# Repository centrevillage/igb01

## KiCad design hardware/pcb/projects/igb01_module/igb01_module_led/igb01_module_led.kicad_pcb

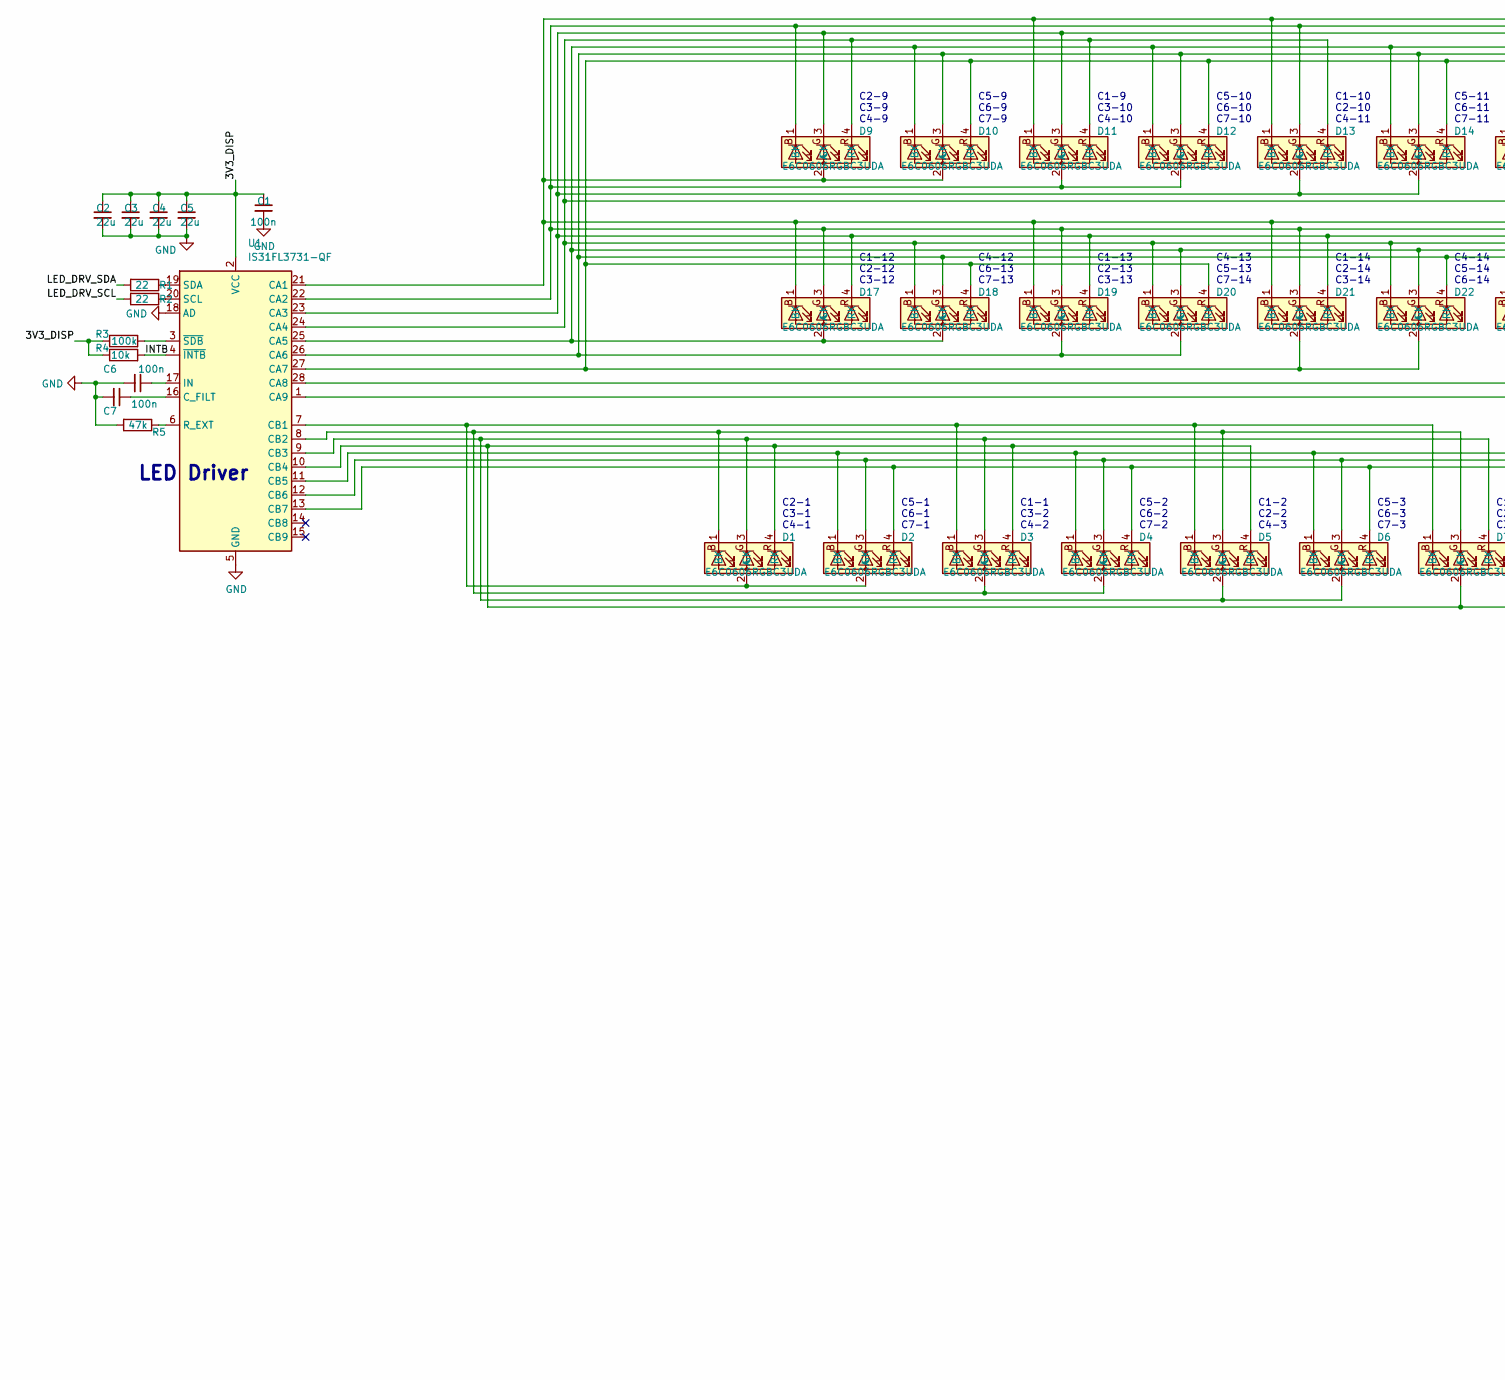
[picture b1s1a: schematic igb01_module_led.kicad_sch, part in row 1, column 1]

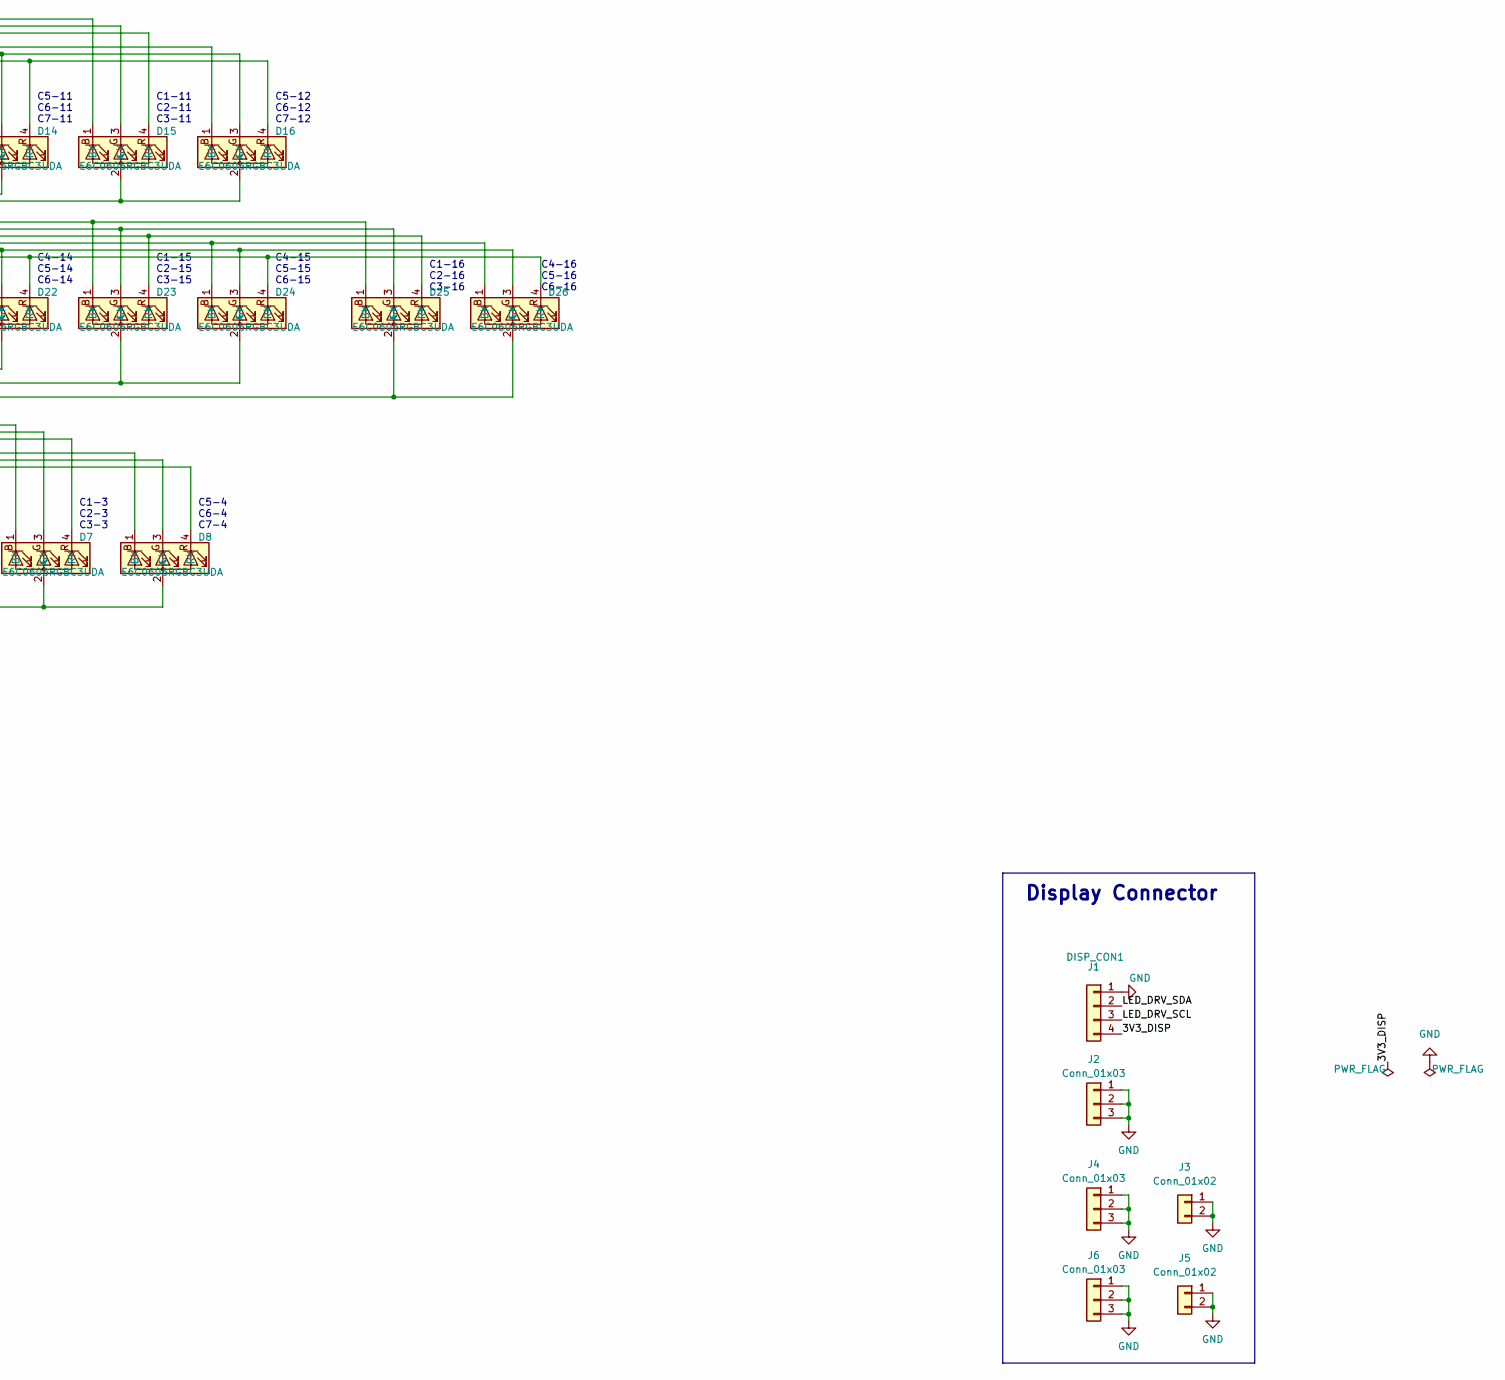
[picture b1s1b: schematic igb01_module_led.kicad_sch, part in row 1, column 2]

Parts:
C1, C6, C7: 100n; C_0402_1005Metric
C2, C3, C4, C5: 22u; C_0805_2012Metric
D1, D2, D3, D4, D5, D6, D7, D8, D9, D10, D11, D12, D13, D14, D15, D16, D17, D18, D19, D20, D21, D22, D23, D24, D25, D26: E6C0606RGBC3UDA; led_rgb
J1: DISP_CON1; PinSocket_1x04_P2.00mm_Vertical
J2, J4, J6: Conn_01x03; PinSocket_1x03_P2.00mm_Vertical
J3, J5: Conn_01x02; PinSocket_1x02_P2.00mm_Vertical
R1, R2: 22; R_0402_1005Metric
R3: 100k; R_0402_1005Metric
R4: 10k; R_0402_1005Metric
R5: 47k; R_0603_1608Metric
U1: IS31FL3731-QF; QFN-28-1EP_4x4mm_P0.4mm_EP2.3x2.3mm

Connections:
/3V3_DISP: C1.1, C2.1, C3.1, C4.1, C5.1, J1.4, R3.1, R4.1, U1.2 (VCC)
/INTB: R4.2, U1.4 (~INTB)
/LED_DRV_SCL: J1.3, R2.2
/LED_DRV_SDA: J1.2, R1.2
GND: C1.2, C2.2, C3.2, C4.2, C5.2, C6.2, C7.2, J1.1, J2.1, J2.2, J2.3, J3.1, J3.2, J4.1, J4.2, J4.3, J5.1, J5.2, J6.1, J6.2, J6.3, R5.2, U1.5 (GND), U1.18 (AD), U1.29 (GND)
unnamed: D1.2 (A), D2.2 (A), D3.1 (BK), D5.1 (BK), D7.1 (BK), U1.7 (CB1)
unnamed: D1.1 (BK), D3.2 (A), D4.2 (A), D5.3 (GK), D7.3 (GK), U1.8 (CB2)
unnamed: D1.3 (GK), D3.3 (GK), D5.2 (A), D6.2 (A), D7.4 (RK), U1.9 (CB3)
unnamed: D1.4 (RK), D3.4 (RK), D5.4 (RK), D7.2 (A), D8.2 (A), U1.10 (CB4)
unnamed: D2.1 (BK), D4.1 (BK), D6.1 (BK), D8.1 (BK), U1.11 (CB5)
unnamed: D2.3 (GK), D4.3 (GK), D6.3 (GK), D8.3 (GK), U1.12 (CB6)
unnamed: D2.4 (RK), D4.4 (RK), D6.4 (RK), D8.4 (RK), U1.13 (CB7)
unnamed: D9.2 (A), D10.2 (A), D11.1 (BK), D13.1 (BK), D15.1 (BK), D17.1 (BK), D19.1 (BK), D21.1 (BK), D23.1 (BK), D25.1 (BK), U1.21 (CA1)
unnamed: D10.1 (BK), D12.1 (BK), D14.1 (BK), D16.1 (BK), D17.2 (A), D18.2 (A), D20.3 (GK), D22.3 (GK), D24.3 (GK), D26.3 (GK), U1.25 (CA5)
unnamed: D10.3 (GK), D12.3 (GK), D14.3 (GK), D16.3 (GK), D18.3 (GK), D19.2 (A), D20.2 (A), D22.4 (RK), D24.4 (RK), D26.4 (RK), U1.26 (CA6)
unnamed: D10.4 (RK), D12.4 (RK), D14.4 (RK), D16.4 (RK), D18.4 (RK), D20.4 (RK), D21.2 (A), D22.2 (A), U1.27 (CA7)
unnamed: D9.1 (BK), D11.2 (A), D12.2 (A), D13.3 (GK), D15.3 (GK), D17.3 (GK), D19.3 (GK), D21.3 (GK), D23.3 (GK), D25.3 (GK), U1.22 (CA2)
unnamed: D9.3 (GK), D11.3 (GK), D13.2 (A), D14.2 (A), D15.4 (RK), D17.4 (RK), D19.4 (RK), D21.4 (RK), D23.4 (RK), D25.4 (RK), U1.23 (CA3)
unnamed: D9.4 (RK), D11.4 (RK), D13.4 (RK), D15.2 (A), D16.2 (A), D18.1 (BK), D20.1 (BK), D22.1 (BK), D24.1 (BK), D26.1 (BK), U1.24 (CA4)
unnamed: D23.2 (A), D24.2 (A), U1.28 (CA8)
unnamed: D25.2 (A), D26.2 (A), U1.1 (CA9)
unnamed: C7.1, U1.16 (C_FILT)
unnamed: C6.1, U1.17 (IN)
unnamed: R5.1, U1.6 (R_EXT)
unnamed: R2.1, U1.20 (SCL)
unnamed: R1.1, U1.19 (SDA)
unnamed: R3.2, U1.3 (~SDB)

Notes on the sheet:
C5-1 C6-1 C7-1
C2-1 C3-1 C4-1
C1-12 C2-12 C3-12
C1-15 C2-15 C3-15
C2-9 C3-9 C4-9
C1-13 C2-13 C3-13
C1-3 C2-3 C3-3
C1-14 C2-14 C3-14
C4-13 C5-13 C7-14
LED Driver
Display Connector
C1-11 C2-11 C3-11
C4-12 C6-13 C7-13
C1-10 C2-10 C4-11
C5-9 C6-9 C7-9
C4-15 C5-15 C6-15
C5-12 C6-12 C7-12
C5-10 C6-10 C7-10
C5-4 C6-4 C7-4
C4-16 C5-16 C6-16
C1-2 C2-2 C4-3
C1-9 C3-10 C4-10
C4-14 C5-14 C6-14
C5-11 C6-11 C7-11
C1-16 C2-16 C3-16
C5-2 C6-2 C7-2
C5-3 C6-3 C7-3
C1-1 C3-2 C4-2

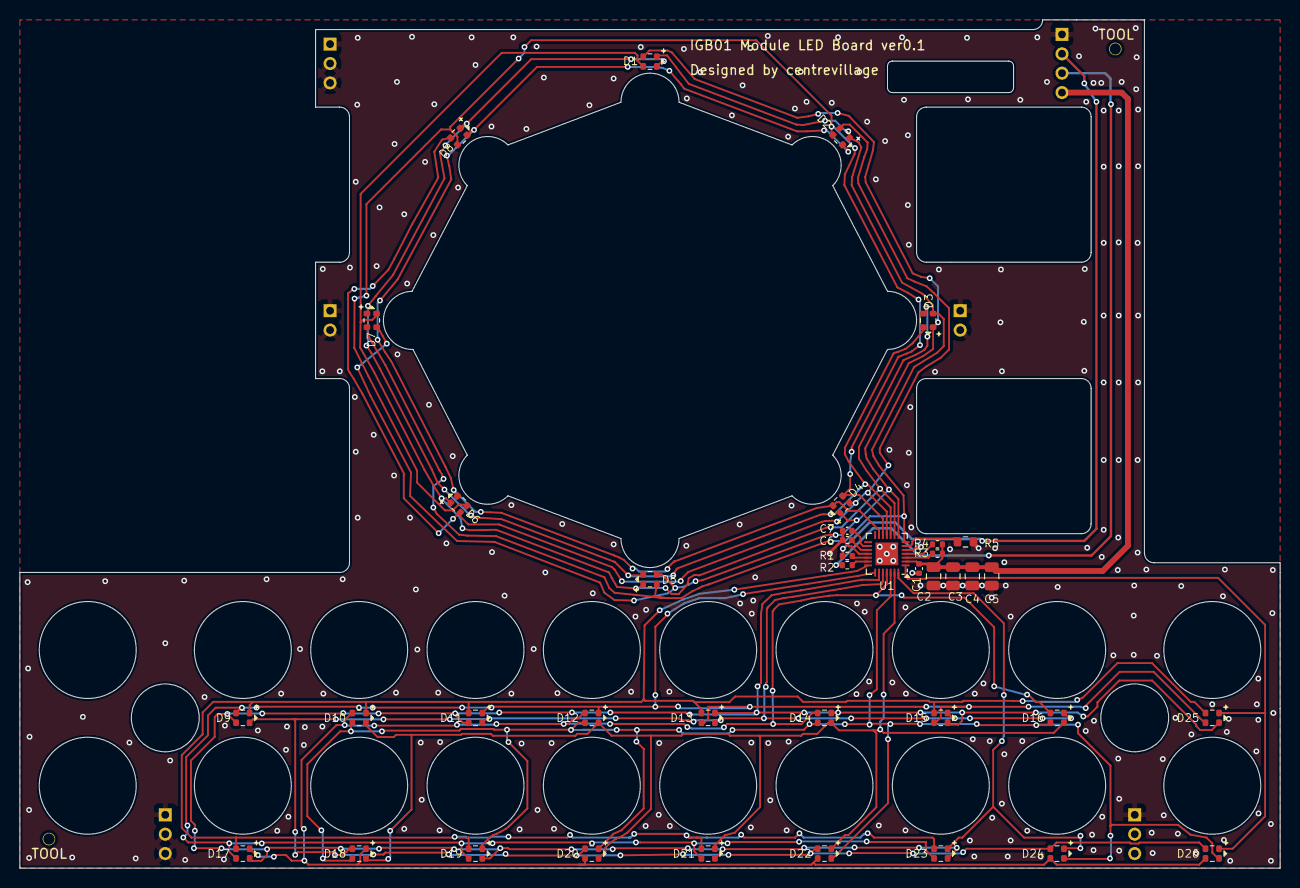
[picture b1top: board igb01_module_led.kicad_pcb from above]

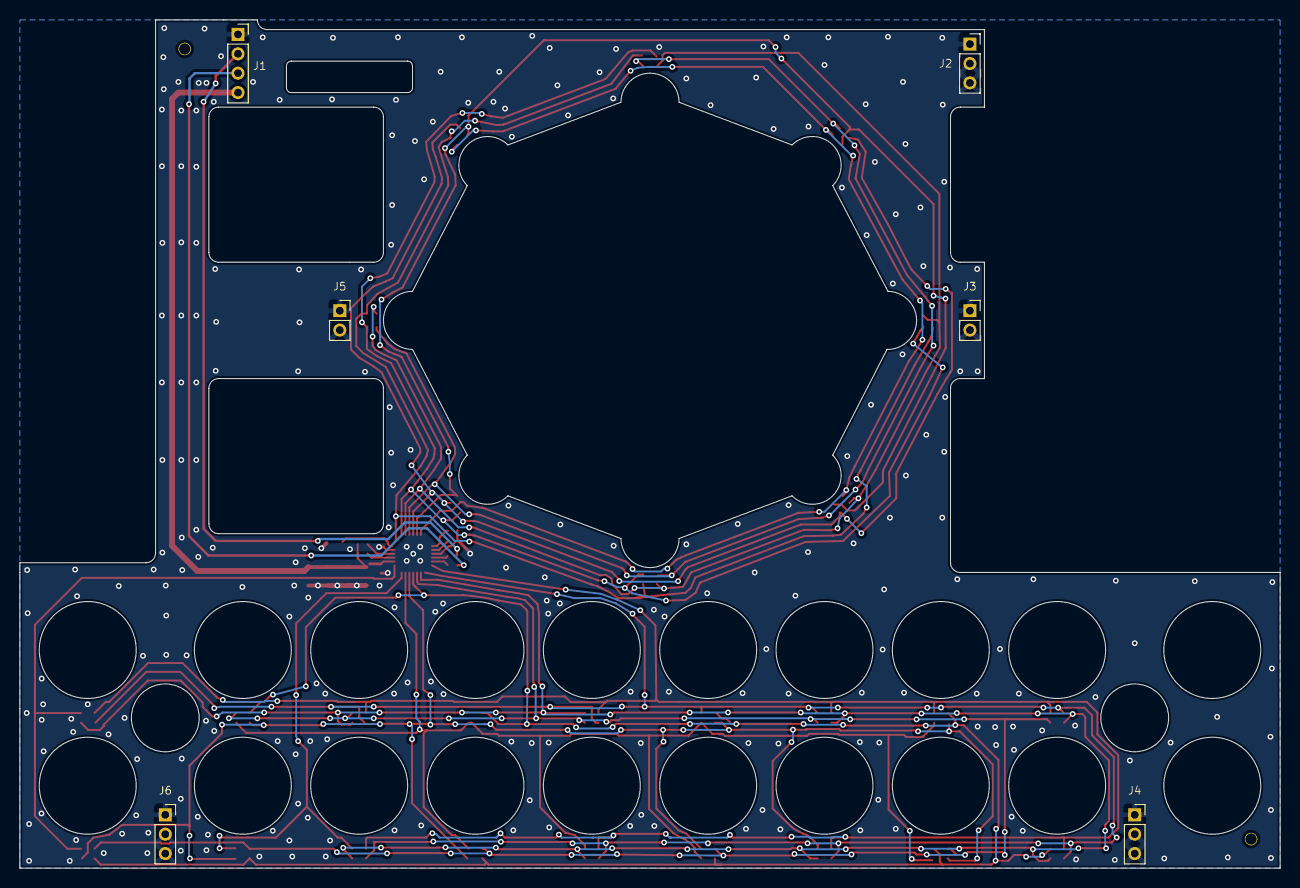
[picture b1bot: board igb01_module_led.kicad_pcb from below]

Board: 2 copper layers, 130.0 x 87.5 mm, 45 parts (6 on the bottom side), 27 nets.

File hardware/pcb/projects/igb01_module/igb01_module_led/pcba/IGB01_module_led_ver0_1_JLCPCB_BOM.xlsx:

Comment | Designator | Footprint | LCSC Part #（optional）
22uF,0805 | C5,C3,C4,C2 | C0805 | C45783
100nF,0402 | C7,C1,C6 | C0402 | C1525
E6C0606RGBC3UDA | D13,D22,D4,D21,D23,D20,D24,D16,D25,D26,D19,D9,D15,D3,D17,D10,D12,D8,D18,D6,D11,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 |  | C375569
22Ω,0402 | R1,R2 | R0402 | C25092
100kΩ,0402 | R3 | R0402 | C25741
10kΩ,0402 | R4 | R0402 | C25744
47kΩ,0603 | R5 | R0603 | C25819
IS31FL3731-QF | U1 | QFN-28 | C191206

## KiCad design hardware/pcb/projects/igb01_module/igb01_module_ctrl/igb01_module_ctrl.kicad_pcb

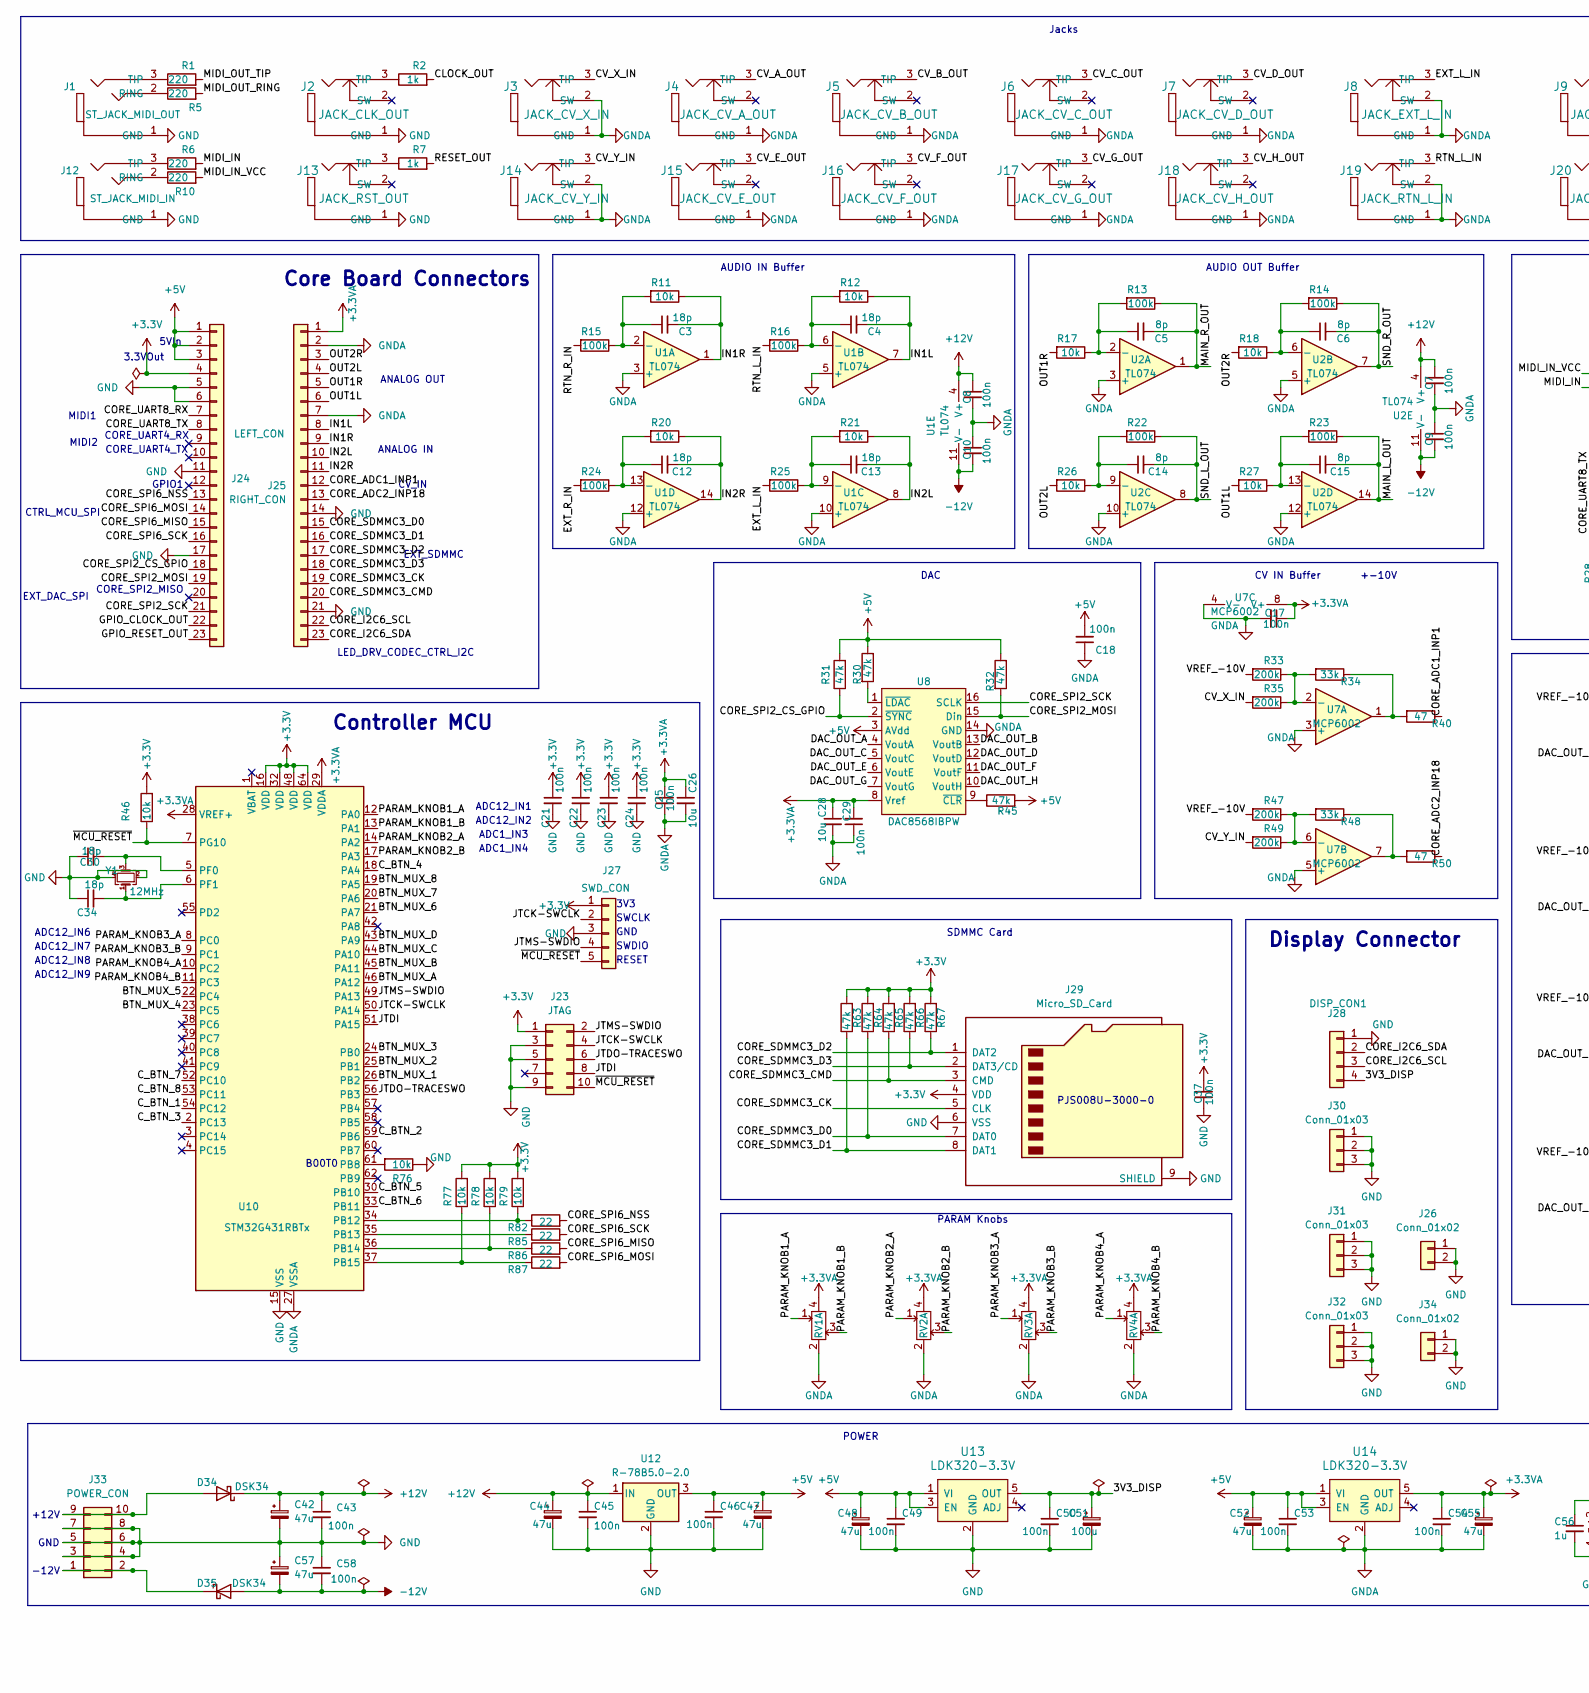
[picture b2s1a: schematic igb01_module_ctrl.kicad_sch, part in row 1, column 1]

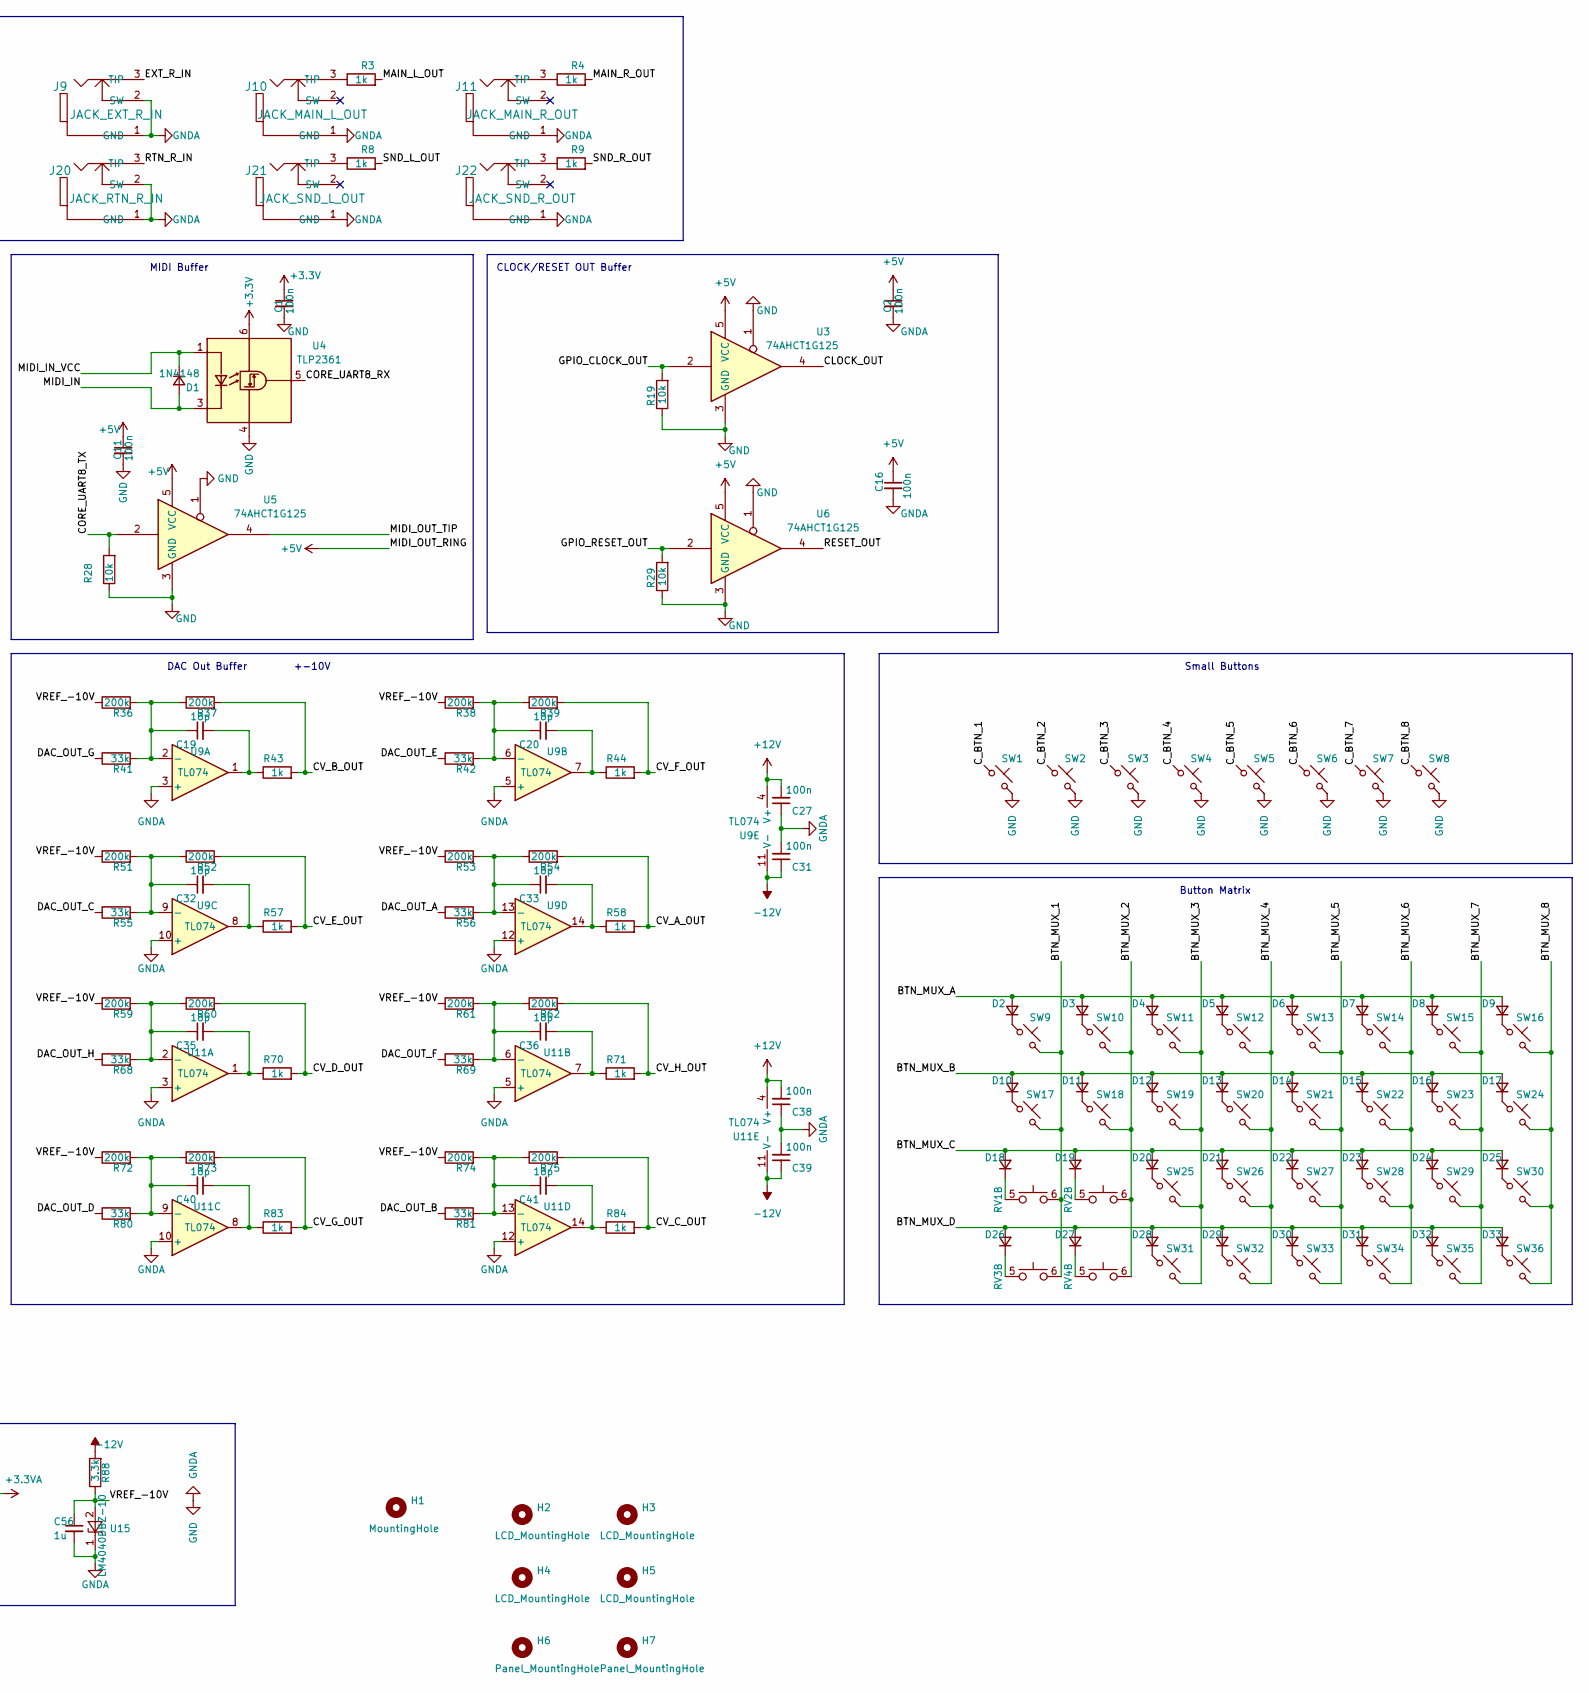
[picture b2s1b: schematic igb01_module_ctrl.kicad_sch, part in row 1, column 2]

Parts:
C1, C2, C7, C8, C9, C10, C11, C16, C17, C18, C21, C22, C23, C24, C25, C27, C29, C31, C37, C38, C39, C43, C45, C46, C49, C50, C53, C54, C58: 100n; C_0603_1608Metric
C3, C4, C12, C13, C19, C20, C30, C32, C33, C34, C35, C36, C40, C41: 18p; C_0603_1608Metric
C5, C6, C14, C15: 8p; C_0603_1608Metric
C26, C28: 10u; C_0805_2012Metric
C42, C44, C47, C48, C52, C55, C57: 47u; C_Elec_5x5.8
C51: 100u; C_Elec_5x5.8
C56: 1u; C_0805_2012Metric
D1: 1N4148; SOD-123
D2, D3, D4, D5, D6, D7, D8, D9, D10, D11, D12, D13, D14, D15, D16, D17, D18, D19, D20, D21, D22, D23, D24, D25, D26, D27, D28, D29, D30, D31, D32, D33: 1N4148; D_SOD-523
D34, D35: DSK34; SOD-123
H1: MountingHole; MountingHole_3.2mm_M3_mod
H2, H3, H4, H5: LCD_MountingHole; MountingHole_2.2mm_M2_mod
H6, H7: Panel_MountingHole; MountingHole_3.2mm_M3_mod
J1: ST_JACK_MIDI_OUT; THONKICONN_center_smleg
J2: JACK_CLK_OUT; THONKICONN_center_smleg
J3: JACK_CV_X_IN; THONKICONN_center_smleg
J4: JACK_CV_A_OUT; THONKICONN_center_smleg
J5: JACK_CV_B_OUT; THONKICONN_center_smleg
J6: JACK_CV_C_OUT; THONKICONN_center_smleg
J7: JACK_CV_D_OUT; THONKICONN_center_smleg
J8: JACK_EXT_L_IN; THONKICONN_center_smleg
J9: JACK_EXT_R_IN; THONKICONN_center_smleg
J10: JACK_MAIN_L_OUT; THONKICONN_center_smleg
J11: JACK_MAIN_R_OUT; THONKICONN_center_smleg
J12: ST_JACK_MIDI_IN; THONKICONN_center_smleg
J13: JACK_RST_OUT; THONKICONN_center_smleg
J14: JACK_CV_Y_IN; THONKICONN_center_smleg
J15: JACK_CV_E_OUT; THONKICONN_center_smleg
J16: JACK_CV_F_OUT; THONKICONN_center_smleg
J17: JACK_CV_G_OUT; THONKICONN_center_smleg
J18: JACK_CV_H_OUT; THONKICONN_center_smleg
J19: JACK_RTN_L_IN; THONKICONN_center_smleg
J20: JACK_RTN_R_IN; THONKICONN_center_smleg
J21: JACK_SND_L_OUT; THONKICONN_center_smleg
J22: JACK_SND_R_OUT; THONKICONN_center_smleg
J23: JTAG; PinHeader_2x05_P1.27mm_Vertical
J24: LEFT_CON; PinSocket_1x23_P2.54mm_Vertical
J25: RIGHT_CON; PinSocket_1x23_P2.54mm_Vertical
J26, J34: Conn_01x02; PinHeader_1x02_P2.00mm_Vertical
J27: SWD_CON; PinSocket_1x05_P2.54mm_Vertical
J28: DISP_CON1; PinHeader_1x04_P2.00mm_Vertical
J29: Micro_SD_Card; MICRO_SD_VERTICAL
J30, J31, J32: Conn_01x03; PinHeader_1x03_P2.00mm_Vertical
J33: POWER_CON; PinHeader_2x05_P2.54mm_Vertical
R1, R5, R6, R10: 220; R_1206_3216Metric
R2, R3, R4, R7, R8, R9, R43, R44, R57, R58, R70, R71, R83, R84: 1k; R_0805_2012Metric
R11, R12, R17, R18, R19, R20, R21, R26, R27, R28, R29, R46, R76, R77, R78, R79: 10k; R_0603_1608Metric
R13, R14, R15, R16, R22, R23, R24, R25: 100k; R_0603_1608Metric
R30, R31, R32, R45, R63, R64, R65, R66, R67: 47k; R_0603_1608Metric
R33, R35, R36, R37, R38, R39, R47, R49, R51, R52, R53, R54, R59, R60, R61, R62, R72, R73, R74, R75: 200k; R_0603_1608Metric
R34, R41, R42, R48, R55, R56, R68, R69, R80, R81: 33k; R_0603_1608Metric
R40, R50: 47; R_0603_1608Metric
R82, R85, R86, R87: 22; R_0603_1608Metric
R88: 3.3k; R_0603_1608Metric
RV1, RV2, RV3, RV4: RV142FPF-40B1
SW1, SW2, SW3, SW4, SW5, SW6, SW7, SW8: SW_Push_45deg; SW_PUSH_6mm_h13mm_mod
SW9, SW10, SW11, SW12, SW13, SW14, SW15, SW16, SW17, SW18, SW19, SW20, SW21, SW22, SW23, SW24, SW25, SW26, SW27, SW28, SW29, SW30, SW31, SW32, SW33, SW34, SW35, SW36: SW_Push_45deg; CandK_Comp_Button
U1, U2, U9, U11: TL074; TSSOP-14_4.4x5mm_P0.65mm
U3, U5, U6: 74AHCT1G125; SOT-23-5
U4: TLP2361; SO-5-6_4.55x3.7mm_P1.27mm
U7: MCP6002; SOIC-8_3.9x4.9mm_P1.27mm
U8: DAC8568IBPW; TSSOP-16_4.4x5mm_P0.65mm
U10: STM32G431RBTx; LQFP-64_10x10mm_P0.5mm
U12: R-78B5.0-2.0; Converter_DCDC_RECOM_R-78B-2.0_THT
U13, U14: LDK320-3.3V; SOT-23-5
U15: LM4040DBZ-10; SOT-23
Y1: 12MHz; Crystal_SMD_2520-4Pin_2.5x2.0mm

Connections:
+3.3V: C1.1, C21.1, C22.1, C23.1, C24.1, C37.1, J23.1, J24.4, J27.1, J29.4 (VDD), R46.2, R63.2, R64.2, R65.2, R66.2, R67.2, R77.2, R78.2, R79.2, U4.6 (VDD), U10.16 (VDD), U10.32 (VDD), U10.48 (VDD), U10.64 (VDD)
+3.3VA: C17.1, C25.1, C26.1, C28.1, C29.2, C54.1, C55.1, J25.1, RV1.4, RV2.4, RV3.4, RV4.4, U7.8 (V+), U8.8 (Vref), U10.28 (VREF+), U10.29 (VDDA), U14.5 (OUT)
+5V: C2.1, C11.1, C16.1, C18.2, C46.1, C47.1, C48.1, C49.1, C52.1, C53.1, J24.1, J24.2, J24.3, R5.2, R30.1, R31.2, R32.1, R45.2, U3.5 (VCC), U5.5 (VCC), U6.5 (VCC), U8.3 (AVdd), U12.3 (OUT), U13.1 (VI), U13.3 (EN), U14.1 (VI), U14.3 (EN)
+12V: C7.1, C8.1, C27.2, C38.2, C42.1, C43.1, C44.1, C45.1, D34.1 (K), U1.4 (V+), U2.4 (V+), U9.4 (V+), U11.4 (V+), U12.1 (IN)
-12V: C9.2, C10.2, C31.1, C39.1, C57.2, C58.2, D35.2 (A), R88.2, U1.11 (V-), U2.11 (V-), U9.11 (V-), U11.11 (V-)
/3V3_DISP: C50.1, C51.1, J28.4, U13.5 (OUT)
/BTN_MUX_1: RV1.6, RV3.6, SW9.2, SW17.2, U10.26 (PB2)
/BTN_MUX_2: RV2.6, RV4.6, SW10.2, SW18.2, U10.25 (PB1)
/BTN_MUX_3: SW11.2, SW19.2, SW25.2, SW31.2, U10.24 (PB0)
/BTN_MUX_4: SW12.2, SW20.2, SW26.2, SW32.2, U10.23 (PC5)
/BTN_MUX_5: SW13.2, SW21.2, SW27.2, SW33.2, U10.22 (PC4)
/BTN_MUX_6: SW14.2, SW22.2, SW28.2, SW34.2, U10.21 (PA7)
/BTN_MUX_7: SW15.2, SW23.2, SW29.2, SW35.2, U10.20 (PA6)
/BTN_MUX_8: SW16.2, SW24.2, SW30.2, SW36.2, U10.19 (PA5)
/BTN_MUX_A: D2.2 (A), D3.2 (A), D4.2 (A), D5.2 (A), D6.2 (A), D7.2 (A), D8.2 (A), D9.2 (A), U10.46 (PA12)
/BTN_MUX_B: D10.2 (A), D11.2 (A), D12.2 (A), D13.2 (A), D14.2 (A), D15.2 (A), D16.2 (A), D17.2 (A), U10.45 (PA11)
/BTN_MUX_C: D18.2 (A), D19.2 (A), D20.2 (A), D21.2 (A), D22.2 (A), D23.2 (A), D24.2 (A), D25.2 (A), U10.44 (PA10)
/BTN_MUX_D: D26.2 (A), D27.2 (A), D28.2 (A), D29.2 (A), D30.2 (A), D31.2 (A), D32.2 (A), D33.2 (A), U10.43 (PA9)
/CLOCK_OUT: R2.2, U3.4
/CORE_ADC1_INP1: J25.12, R40.1
/CORE_ADC2_INP18: J25.13, R50.1
/CORE_I2C6_SCL: J25.22, J28.3
/CORE_I2C6_SDA: J25.23, J28.2
/CORE_SDMMC3_CK: J25.19, J29.5 (CLK)
/CORE_SDMMC3_CMD: J25.20, J29.3 (CMD), R65.1
/CORE_SDMMC3_D0: J25.15, J29.7 (DAT0), R64.1
/CORE_SDMMC3_D1: J25.16, J29.8 (DAT1), R63.1
/CORE_SDMMC3_D2: J25.17, J29.1 (DAT2), R67.1
/CORE_SDMMC3_D3: J25.18, J29.2 (DAT3/CD), R66.1
/CORE_SPI2_CS_GPIO: J24.18, R31.1, U8.2 (~SYNC)
/CORE_SPI2_MOSI: J24.19, R32.2, U8.15 (Din)
/CORE_SPI2_SCK: J24.21, U8.16 (SCLK)
/CORE_SPI6_MISO: J24.15, R86.2
/CORE_SPI6_MOSI: J24.14, R87.2
/CORE_SPI6_NSS: J24.13, R82.2
/CORE_SPI6_SCK: J24.16, R85.2
/CORE_UART8_RX: J24.7, U4.5 (VO)
/CORE_UART8_TX: J24.8, R28.2, U5.2
/CV_A_OUT: J4.3 (TIP), R54.2, R58.2
/CV_B_OUT: J5.3 (TIP), R37.2, R43.2
/CV_C_OUT: J6.3 (TIP), R75.2, R84.2
/CV_D_OUT: J7.3 (TIP), R60.2, R70.2
/CV_E_OUT: J15.3 (TIP), R52.2, R57.2
/CV_F_OUT: J16.3 (TIP), R39.2, R44.2
/CV_G_OUT: J17.3 (TIP), R73.2, R83.2
/CV_H_OUT: J18.3 (TIP), R62.2, R71.2
/CV_X_IN: J3.3 (TIP), R35.2
/CV_Y_IN: J14.3 (TIP), R49.2
/C_BTN_1: SW1.1, U10.54 (PC12)
/C_BTN_2: SW2.1, U10.59 (PB6)
/C_BTN_3: SW3.1, U10.2 (PC13)
/C_BTN_4: SW4.1, U10.18 (PA4)
/C_BTN_5: SW5.1, U10.30 (PB10)
/C_BTN_6: SW6.1, U10.33 (PB11)
/C_BTN_7: SW7.1, U10.52 (PC10)
/C_BTN_8: SW8.1, U10.53 (PC11)
/DAC_OUT_A: R56.1, U8.4 (VoutA)
/DAC_OUT_B: R81.1, U8.13 (VoutB)
/DAC_OUT_C: R55.1, U8.5 (VoutC)
/DAC_OUT_D: R80.1, U8.12 (VoutD)
/DAC_OUT_E: R42.1, U8.6 (VoutE)
/DAC_OUT_F: R69.1, U8.11 (VoutF)
/DAC_OUT_G: R41.1, U8.7 (VoutG)
/DAC_OUT_H: R68.1, U8.10 (VoutH)
/EXT_L_IN: J8.3 (TIP), R25.2
/EXT_R_IN: J9.3 (TIP), R24.2
/GPIO_CLOCK_OUT: J24.22, R19.2, U3.2
/GPIO_RESET_OUT: J24.23, R29.2, U6.2
/IN1L: C4.2, J25.8, R12.1, U1.7
/IN1R: C3.2, J25.9, R11.1, U1.1
/IN2L: C13.2, J25.10, R21.1, U1.8
/IN2R: C12.2, J25.11, R20.1, U1.14
/JTCK-SWCLK: J23.4, J27.2, U10.50 (PA14)
/JTDI: J23.8, U10.51 (PA15)
/JTDO-TRACESWO: J23.6, U10.56 (PB3)
/JTMS-SWDIO: J23.2, J27.4, U10.49 (PA13)
/MAIN_L_OUT: C15.2, R3.2, R23.1, U2.14
/MAIN_R_OUT: C5.2, R4.2, R13.1, U2.1
/MIDI_IN: D1.2 (A), R6.2, U4.3 (K)
/MIDI_IN_VCC: D1.1 (K), R10.2, U4.1 (A)
/MIDI_OUT_TIP: R1.2, U5.4
/OUT1L: J25.6, R27.2
/OUT1R: J25.5, R17.2
/OUT2L: J25.4, R26.2
/OUT2R: J25.3, R18.2
/PARAM_KNOB1_A: RV1.1, U10.12 (PA0)
/PARAM_KNOB1_B: RV1.3, U10.13 (PA1)
/PARAM_KNOB2_A: RV2.1, U10.14 (PA2)
/PARAM_KNOB2_B: RV2.3, U10.17 (PA3)
/PARAM_KNOB3_A: RV3.1, U10.8 (PC0)
/PARAM_KNOB3_B: RV3.3, U10.9 (PC1)
/PARAM_KNOB4_A: RV4.1, U10.10 (PC2)
/PARAM_KNOB4_B: RV4.3, U10.11 (PC3)
/RESET_OUT: R7.2, U6.4
/RTN_L_IN: J19.3 (TIP), R16.2
/RTN_R_IN: J20.3 (TIP), R15.2
/SND_L_OUT: C14.2, R8.2, R22.1, U2.8
/SND_R_OUT: C6.2, R9.2, R14.1, U2.7
/VREF_-10V: C56.1, R33.2, R36.1, R38.1, R47.2, R51.1, R53.1, R59.1, R61.1, R72.1, R74.1, R88.1, U15.2 (A)
/~MCU_RESET: J23.10, J27.5, R46.1, U10.7 (PG10)
GND: C1.2, C2.2, C7.2, C8.2, C9.1, C10.1, C11.2, C16.2, C17.2, C18.1, C21.2, C22.2, C23.2, C24.2, C25.2, C26.2, C27.1, C28.2, C29.1, C30.1, C31.2, C34.1, C37.2, C38.1, C39.2, C42.2, C43.2, C44.2, C45.2, C46.2, C47.2, C48.2, C49.2, C50.2, C51.2, C52.2, C53.2, C54.2, C55.2, C56.2, C57.1, C58.1, J1.1 (GND), J2.1 (GND), J3.1 (GND), J3.2 (SW), J4.1 (GND), J5.1 (GND), J6.1 (GND), J7.1 (GND), J8.1 (GND), J8.2 (SW), J9.1 (GND), J9.2 (SW), J10.1 (GND), J11.1 (GND), J12.1 (GND), J13.1 (GND), J14.1 (GND), J14.2 (SW), J15.1 (GND), J16.1 (GND), J17.1 (GND), J18.1 (GND), J19.1 (GND), J19.2 (SW), J20.1 (GND), J20.2 (SW), J21.1 (GND), J22.1 (GND), J23.3, J23.5, J23.9, J24.5, J24.6, J24.11, J24.17, J25.2, J25.7, J25.14, J25.21, J26.1, J26.2, J27.3, J28.1, J29.6 (VSS), J29.9 (SHIELD), J30.1, J30.2, J30.3, J31.1, J31.2, J31.3, J32.1, J32.2, J32.3, J33.3, J33.4, J33.5, J33.6, J33.7, J33.8, J34.1, J34.2, R19.1, R28.1, R29.1, R76.1, RV1.2, RV2.2, RV3.2, RV4.2, SW1.2, SW2.2, SW3.2, SW4.2, SW5.2, SW6.2, SW7.2, SW8.2, U1.3 (+), U1.5 (+), U1.10 (+), U1.12 (+), U2.3 (+), U2.5 (+), U2.10 (+), U2.12 (+), U3.1, U3.3 (GND), U4.4 (GND), U5.1, U5.3 (GND), U6.1, U6.3 (GND), U7.3 (+), U7.4 (V-), U7.5 (+), U8.14 (GND), U9.3 (+), U9.5 (+), U9.10 (+), U9.12 (+), U10.15 (VSS), U10.27 (VSSA), U10.31 (VSS), U10.47 (VSS), U10.63 (VSS), U11.3 (+), U11.5 (+), U11.10 (+), U11.12 (+), U12.2 (GND), U13.2 (GND), U14.2 (GND), U15.1 (K), Y1.2, Y1.4
unnamed: C19.2, R43.1, U9.1
unnamed: C20.2, R44.1, U9.7
unnamed: C32.2, R57.1, U9.8
unnamed: C33.2, R58.1, U9.14
unnamed: C35.2, R70.1, U11.1
unnamed: C36.2, R71.1, U11.7
unnamed: C40.2, R83.1, U11.8
unnamed: C41.2, R84.1, U11.14
unnamed: D2.1 (K), SW9.1
unnamed: D3.1 (K), SW10.1
unnamed: D4.1 (K), SW11.1
unnamed: D5.1 (K), SW12.1
unnamed: D6.1 (K), SW13.1
unnamed: D7.1 (K), SW14.1
unnamed: D8.1 (K), SW15.1
unnamed: D9.1 (K), SW16.1
unnamed: D10.1 (K), SW17.1
unnamed: D11.1 (K), SW18.1
unnamed: D12.1 (K), SW19.1
unnamed: D13.1 (K), SW20.1
unnamed: D14.1 (K), SW21.1
unnamed: D15.1 (K), SW22.1
unnamed: D16.1 (K), SW23.1
unnamed: D17.1 (K), SW24.1
unnamed: D18.1 (K), RV1.5
unnamed: D19.1 (K), RV2.5
unnamed: D20.1 (K), SW25.1
unnamed: D21.1 (K), SW26.1
unnamed: D22.1 (K), SW27.1
unnamed: D23.1 (K), SW28.1
unnamed: D24.1 (K), SW29.1
unnamed: D25.1 (K), SW30.1
unnamed: D26.1 (K), RV3.5
unnamed: D27.1 (K), RV4.5
unnamed: D28.1 (K), SW31.1
unnamed: D29.1 (K), SW32.1
unnamed: D30.1 (K), SW33.1
unnamed: D31.1 (K), SW34.1
unnamed: D32.1 (K), SW35.1
unnamed: D33.1 (K), SW36.1
unnamed: D34.2 (A), J33.9, J33.10
unnamed: D35.1 (K), J33.1, J33.2
unnamed: J1.2 (RING), R5.1
unnamed: J1.3 (TIP), R1.1
unnamed: J2.3 (TIP), R2.1
unnamed: J10.3 (TIP), R3.1
unnamed: J11.3 (TIP), R4.1
unnamed: J12.2 (RING), R10.1
unnamed: J12.3 (TIP), R6.1
unnamed: J13.3 (TIP), R7.1
unnamed: J21.3 (TIP), R8.1
unnamed: J22.3 (TIP), R9.1
unnamed: R34.1, R40.2, U7.1
unnamed: R48.1, R50.2, U7.7
unnamed: C3.1, R11.2, R15.1, U1.2 (-)
unnamed: C4.1, R12.2, R16.1, U1.6 (-)
unnamed: C13.1, R21.2, R25.1, U1.9 (-)
unnamed: C12.1, R20.2, R24.1, U1.13 (-)
unnamed: C5.1, R13.2, R17.1, U2.2 (-)
unnamed: C6.1, R14.2, R18.1, U2.6 (-)
unnamed: C14.1, R22.2, R26.1, U2.9 (-)
unnamed: C15.1, R23.2, R27.1, U2.13 (-)
unnamed: R33.1, R34.2, R35.1, U7.2 (-)
unnamed: R47.1, R48.2, R49.1, U7.6 (-)
unnamed: R45.1, U8.9 (~CLR)
unnamed: R30.2, U8.1 (~LDAC)
unnamed: C19.1, R36.2, R37.1, R41.2, U9.2 (-)
unnamed: C20.1, R38.2, R39.1, R42.2, U9.6 (-)
unnamed: C32.1, R51.2, R52.1, R55.2, U9.9 (-)
unnamed: C33.1, R53.2, R54.1, R56.2, U9.13 (-)
unnamed: R76.2, U10.61 (PB8)
unnamed: R79.1, R82.1, U10.34 (PB12)
unnamed: R85.1, U10.35 (PB13)
unnamed: R78.1, R86.1, U10.36 (PB14)
unnamed: R77.1, R87.1, U10.37 (PB15)
unnamed: C30.2, U10.5 (PF0), Y1.3
unnamed: C34.2, U10.6 (PF1), Y1.1
unnamed: C35.1, R59.2, R60.1, R68.2, U11.2 (-)
unnamed: C36.1, R61.2, R62.1, R69.2, U11.6 (-)
unnamed: C40.1, R72.2, R73.1, R80.2, U11.9 (-)
unnamed: C41.1, R74.2, R75.1, R81.2, U11.13 (-)

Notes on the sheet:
ANALOG IN
AUDIO IN Buffer
ADC12_IN6
SWCLK
ADC1_IN3
GPIO1
CV_IN
-12V
Small Buttons
3V3
DAC
PARAM Knobs
DAC Out Buffer
CORE_UART4_TX
5VIn
PJS008U-3000-0
EXT_DAC_SPI
3.3VOut
GND
Button Matrix
CORE_UART4_RX
Jacks
+-10V
ADC12_IN8
ADC1_IN4
SDMMC Card
Core Board Connectors
CV IN Buffer
RESET
B00T0
CTRL_MCU_SPI
CLOCK/RESET OUT Buffer
EXT_SDMMC
ADC12_IN7
ADC12_IN9
MIDI2
ANALOG OUT
MIDI Buffer
Controller MCU
CORE_SPI2_MISO
